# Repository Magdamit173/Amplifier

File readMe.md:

# Multi-Stage BJT Amplifier (v2.0)

A high-gain, dual-stage BJT amplifier project designed for the **Stage II (March 26)** milestone. This design is optimized for fabrication on a **presensitized PCB** with a compact footprint.

### Design Specifications
* **Target Gain ($A_v$):** $\ge 120$
* **Frequency Range (Ideal):** $80\text{Hz}$ to $20\text{kHz}$
* **Board Dimensions:** $2.2480 \times 1.1496$ inches
* **Trace Clearance:** $0.300\text{mm}$ ~ $0.400\text{mm}$ 
* **Track Width:** $0.850\text{mm}$ ~ $1.000\text{mm}$ 
* **Filled Zone (Notice ⚠️):** $0.400\text{mm}$
* **Fabrication Method:** Presensitized PCB

| Contributors | Main Role | Responsibilities |
| --- | --- | --- | 
| Anday, John Kevin I. | Logistics |Component sourcing and technical specification sourcing. |
| Haque, Majeed P. | Technical Director (Leader) [Amplifier Circuit](/NI%20Multisim/Amplifier.ms14) | Mathematical modeling, circuit analysis, and core calculations. |
| Leonardo, John Ruiz | Quality Assurance |Validation of engineering calculations and design accuracy.|
| Magdamit, Rovic | Hardware/PCB, and Documentation [github](./)| Design layout, footprint selection. |
| Obar, Tohms Hegel V. | Documentation Head | Technical reporting, citation research, and presentation design.|

### Component Notes
* **Coupling Capacitors:** 10µF 50V **Monolithic Ceramics** (Code 106).
* **Bypass Capacitors:** 33µF **16V** Electrolytics.
* **Note:** Monolithic capacitors are utilized in this design as the primary representation for high-value ceramic components to ensure a compact and stable PCB layout.

### Components (Table of Expense)

| Category | Component Description | Qty | Unit Price (PHP) | Total (PHP) | Reference Link |
| :--- | :--- | :---: | :---: | :---: | :--- |
| **Active** | BC547 NPN Transistor (Unsorted) | 1 | ₱0.83 | ₱0.83 | [Shopee (100pcs)](https://shopee.ph/100pcs-BC547-TO-92-NPN-transistor-i.119376932.27625517704) |
| **Active** | 2N3904 NPN Transistor | 1 | ₱0.96 | ₱0.96 | [Shopee (50pcs)](https://shopee.ph/50PCS-2N3904-2N3906-2N4403-2N2907-2N4401-2N2222-PN2222-2N5401-2N5551-TO-92-TO92-Transistor-New-i.1130255612.20395632930) |
| **Capacitors** | 10µF 50V Monolithic Ceramic (106) | 3 | ₱0.98 | ₱2.94 | [Shopee (50pcs)](https://shopee.ph/product/497215439/24193377802) |
| **Capacitors** | 33µF 16V Electrolytic | 2 | ₱3.60 | ₱7.20 | [Shopee (5pcs)](https://shopee.ph/Electrolytic-Capacitor-16V-25V-35V-50V-i.535662606.26003134704) |
| **Resistors** | 1/4W Metal Film Resistors | 11 | ₱3.00 | ₱33.00 | Local Retail |
| **Connectors** | 2-Pin Screw Terminal (5.0mm) | 3 | ₱4.20 | ₱12.60 | [Shopee (10pcs)](https://shopee.ph/10Pcs-KF301-2P-Screw-5.0mm-Terminal-Block-i.487295469.12046517038) |
| **Fabrication**| **Presensitized PCB (4x6 inches)** | 1 | **₱205.00** | **₱205.00** | [Lazada (Alexan)](https://www.lazada.com.ph/products/with-developer-alexan-presensitized-pcb-4x6-i1380024544.html) |
| **TOTAL** | | | | **₱261.53** | |

*Note: Unit prices are derived from bulk pack listings (Shopee/Lazada) to reflect actual prototype cost.*

### Design Documentation

#### Schematic Diagram

### PCB Layout & 3D Preview
| 2D Copper Trace View | 3D Rendered View |
| :--- | :--- |
|  |  |

### Repository Structure
* **`/Plot`**: Contains exported manufacturing files (SVG/PNG).

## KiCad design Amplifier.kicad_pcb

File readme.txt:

BC547 100pcs (unsorted) - ₱83 : https://shopee.ph/100pcs-BC547-TO-92-NPN-transistor-i.119376932.27625517704

2N3904 50pcs - ₱48 : https://shopee.ph/50PCS-2N3904-2N3906-2N4403-2N2907-2N4401-2N2222-PN2222-2N5401-2N5551-TO-92-TO92-Transistor-New-i.1130255612.20395632930

Monolithic Ceramic Capacitor (10uf 50v) 50pcs - ₱49 : https://shopee.ph/product/497215439/24193377802?d_id=2e233&uls_trackid=5506nlvd01pl&utm_content=AAiY7dA1AcTbPeZJHS294Lu2gis

Electrolytic capacitor (33uf 16v) 5pcs - 18 pesos: 
https://shopee.ph/Electrolytic-Capacitor-16V-25V-35V-50V-with-various-capacitance-i.535662606.26003134704?extraParams=%7B%22display_model_id%22%3A234210111310%2C%22model_selection_logic%22%3A3%7D&sp_atk=d5a8819d-56a0-4e3d-8631-ebf6dfb6370a&xptdk=d5a8819d-56a0-4e3d-8631-ebf6dfb6370a

1/4W Metal Film Resistors 11pcs : Can be bought on local stores, each 1 wouldn't be greater than 2 pesos

screw terminal 10Pcs -  42 pesos: https://shopee.ph/10Pcs-KF301-2P-Screw-5.0mm-Terminal-Block-2-Pin-3-Pin-Pcb-Terminal-Block-Connector-i.487295469.12046517038

Alexan Presensitized PCB (4"x6") - ₱205 : https://www.lazada.com.ph/products/with-developer-alexan-presensitized-pcb-4x6-i1380024544.html

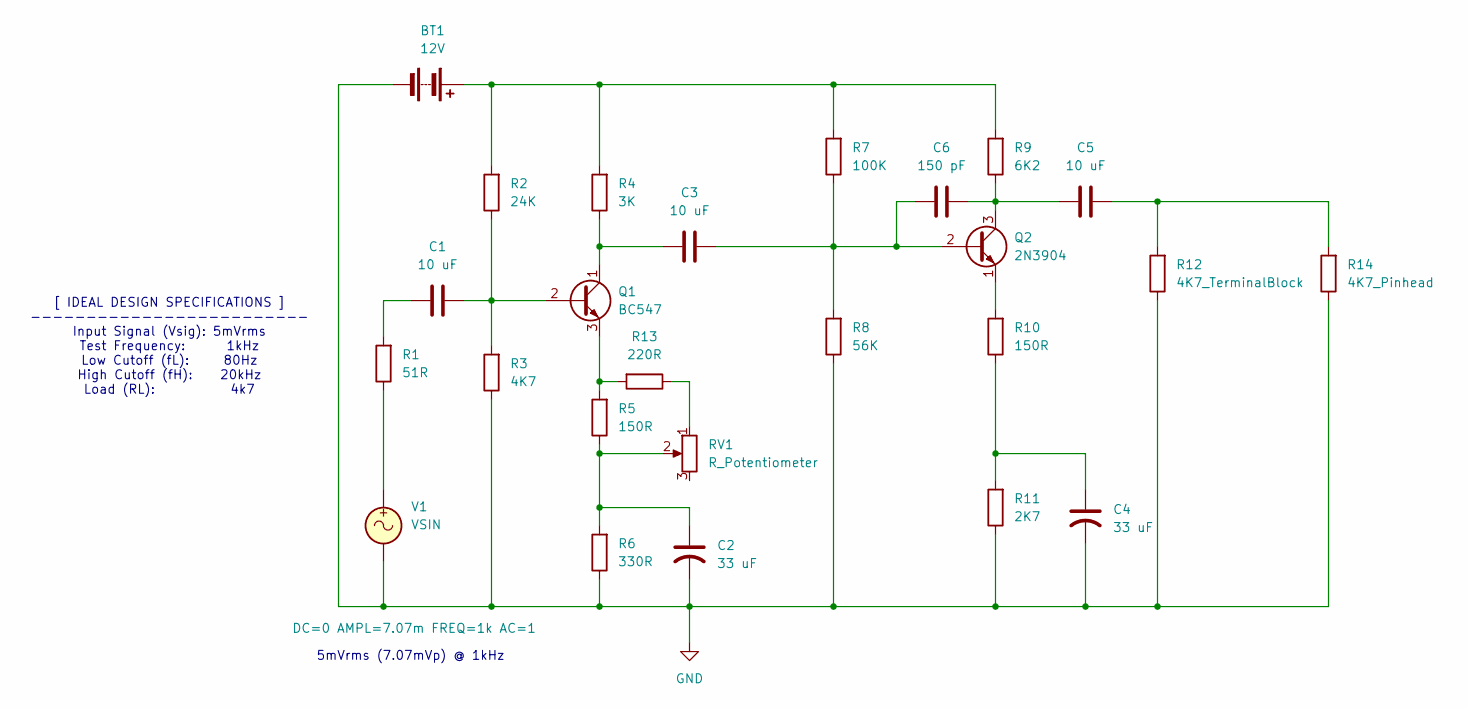
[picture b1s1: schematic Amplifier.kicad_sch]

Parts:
BT1: 12V; TerminalBlock_Phoenix_MKDS-1,5-2_1x02_P5.00mm_Horizontal
C1, C3, C5: 10 uF; C_Disc_D4.3mm_W1.9mm_P5.00mm
C2, C4: 33 uF; CP_Radial_D5.0mm_P2.00mm
C6: 150 pF; C_Disc_D4.3mm_W1.9mm_P5.00mm
Q1: BC547; TO-92_Inline
Q2: 2N3904; TO-92_Inline
R1: 51R; R_Axial_DIN0207_L6.3mm_D2.5mm_P10.16mm_Horizontal
R2: 24K; R_Axial_DIN0207_L6.3mm_D2.5mm_P10.16mm_Horizontal
R3: 4K7; R_Axial_DIN0207_L6.3mm_D2.5mm_P10.16mm_Horizontal
R4: 3K; R_Axial_DIN0207_L6.3mm_D2.5mm_P10.16mm_Horizontal
R5, R10: 150R; R_Axial_DIN0207_L6.3mm_D2.5mm_P10.16mm_Horizontal
R6: 330R; R_Axial_DIN0207_L6.3mm_D2.5mm_P10.16mm_Horizontal
R7: 100K; R_Axial_DIN0207_L6.3mm_D2.5mm_P10.16mm_Horizontal
R8: 56K; R_Axial_DIN0207_L6.3mm_D2.5mm_P10.16mm_Horizontal
R9: 6K2; R_Axial_DIN0207_L6.3mm_D2.5mm_P10.16mm_Horizontal
R11: 2K7; R_Axial_DIN0207_L6.3mm_D2.5mm_P10.16mm_Horizontal
R12: 4K7_TerminalBlock; TerminalBlock_Phoenix_MKDS-1,5-2_1x02_P5.00mm_Horizontal
R13: 220R; R_Axial_DIN0207_L6.3mm_D2.5mm_P10.16mm_Horizontal
R14: 4K7_Pinhead; PinHeader_1x02_P2.54mm_Vertical
RV1: R_Potentiometer; TerminalBlock_Phoenix_MKDS-1,5-2_1x02_P5.00mm_Horizontal
V1: VSIN; TerminalBlock_Phoenix_MKDS-1,5-2_1x02_P5.00mm_Horizontal

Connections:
GND: BT1.2 (-), C2.2, C4.2, R3.1, R6.1, R8.1, R11.1, R12.1, R14.1, V1.2
unnamed: BT1.1 (+), R2.2, R4.2, R7.2, R9.2
unnamed: C1.1, R1.2
unnamed: C2.1, R5.1, R6.2, RV1.2
unnamed: C4.1, R10.1, R11.2
unnamed: C5.1, R12.2, R14.2
unnamed: C1.2, Q1.2 (B), R2.1, R3.2
unnamed: C3.1, Q1.1 (C), R4.1
unnamed: Q1.3 (E), R5.2, R13.2
unnamed: C3.2, C6.2, Q2.2 (B), R7.1, R8.2
unnamed: C5.2, C6.1, Q2.3 (C), R9.1
unnamed: Q2.1 (E), R10.2
unnamed: R1.1, V1.1
unnamed: R13.1, RV1.1

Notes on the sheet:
[ IDEAL DESIGN SPECIFICATIONS ] ------------------------- Input Signal (Vsig): 5mVrms Test Frequency: 1kHz Low Cutoff (fL): 80Hz High Cutoff (fH): 20kHz Load (RL): 4k7
5mVrms (7.07mVp) @ 1kHz

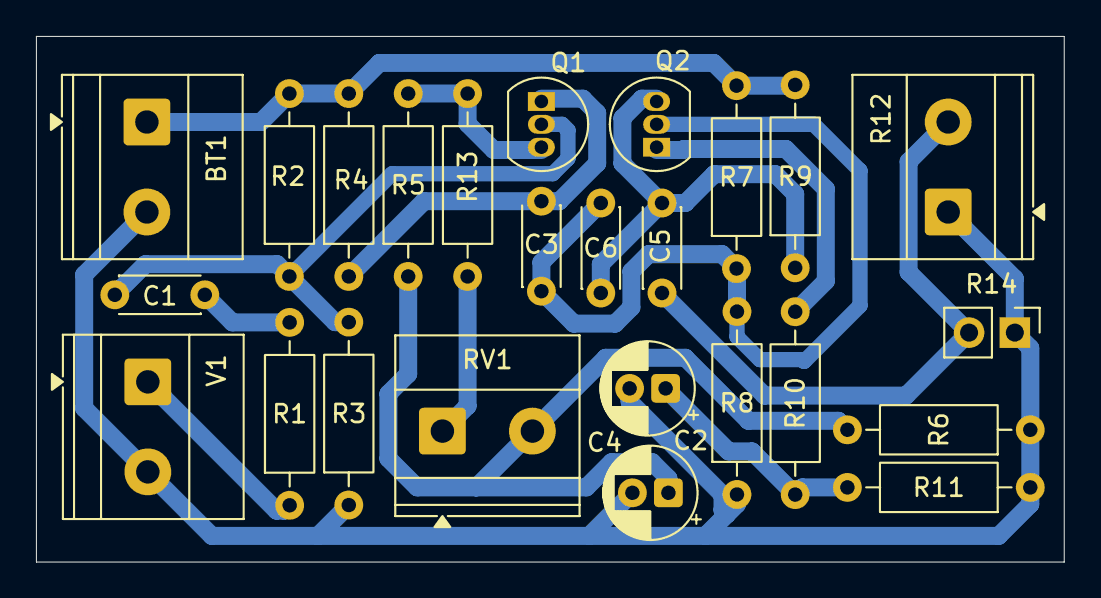
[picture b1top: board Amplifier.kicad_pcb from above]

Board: 2 copper layers, 57.1 x 29.2 mm, 25 parts (0 on the bottom side), 14 nets.

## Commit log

2026-02-21 version 1: 2.22.2026
2026-02-22 version 1.0: 2.22.2026
2026-02-26 Change title from 'Power Amplifier' to 'Amplifier'
    Updated the title to reflect the project as an amplifier.
2026-02-26 2.26.2026
2026-03-23 v2.0 3.24.2026
